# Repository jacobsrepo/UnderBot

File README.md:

# UnderBot

Robot models, ROS 2 / Foxglove station, perception and memory, navigation simulation, and electrical design sources. Existing development lines are preserved; see [the project map](docs/PROJECT_MAP.md) for their roles and [local setup](docs/LOCAL_SETUP.md) for this PC's working installations.

## Components

| Folder | Purpose |
| --- | --- |
| `compact_lab_rover/` | Original parametric rover URDF, RViz configuration and model generator |
| `robot_station/` | ROS gateway, telemetry demo, Qwen chat, bounded world state, memory integration and navigation executor |
| `robot-station-extension/` | Foxglove controls, chat, simulation navigation and telemetry UI |
| `perception/` | EMEET camera/YOLO pipeline, audio transport, Pi communications and PostgreSQL recognition memory |
| `navigation/` | Sample-map preparation, derived demo map, Foxglove layout and navigation documentation |
| `hardware/electrical/` | Versioned KiCad schematics, carrier/PCB designs, budgets and review reports |
| `models/` | Preserved R08/R09 packages, final exports and historical FreeCAD concepts |
| `desktop/` | Cortex desktop assistant, imported with its complete development history |
| `ros2_subsystem/` | Alternative ROS 2 workspace, dashboard and VLA node |
| `website/` | Project website and navigation demonstration video |
| `tools/windows/` | Preserved Windows launchers, deployment overrides and shared ROS environment manifest |

## Getting started

- [Station setup and topic contract](robot_station/README.md)
- [Qwen chat and memory behavior](robot_station/AI_CHAT.md)
- [Navigation simulation and supported commands](navigation/README.md)
- [Camera, audio and perception](perception/README.md)
- [Recognition memory](perception/memory/README.md)
- [Electrical design and revision history](hardware/electrical/README.md)
- [Team workflow](CONTRIBUTING.md)

## Implementation boundaries

Camera and audio pipelines can use real devices. Navigation demonstrations use simulated robot pose and motion on a sample map; they are not physical navigation, SLAM or validated robot dynamics. General chat uses Ollama when configured. Recognition memory requires private database configuration and enrollment. Hardware forwarding remains disabled by default.

The repository contains alternative robot models and implementation lines, not a single fully integrated autonomous robot. Electrical review reports and CAD checks do not establish hardware ratings or readiness to energize. Existing documentation records historical tests; see [current validation](docs/VALIDATION.md) for checks performed during consolidation.

Dependencies, credentials, personal memory databases, recordings and local tool installations are excluded from Git. Original source revisions and development branches remain available. MATLAB/Simulink modelling is the next task and has not been started here.

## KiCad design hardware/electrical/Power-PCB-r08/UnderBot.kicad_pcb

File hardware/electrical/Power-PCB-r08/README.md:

# UnderBot power-distribution PCB r08

**UNROUTED PLACEMENT DRAFT — NOT FOR FABRICATION.** This is the first physical PCB artifact, not a working board. No Gerbers released. All converter modules are external, connected by rated harnesses; this board distributes fused nominal12V. It does not yet mount converters or generate5V/3.3V itself.

## Board and circuit
100 x90 mm outline; two copper layers proposed; four3.2mm mounting holes. Six2-way terminals and four MINI fuse holders. Footprints have assigned nets and schematic references. Ratsnest/unconnected DRC findings are expected because copper routing has deliberately not been finalized before protection/current/connector review. A3 circuit PDF accompanies the PCB.

J1 pin1 = protected input positive; pin2 = ground. NOCO approved accessory cable, external main fuse, disconnect and qualified polarity protection are REQUIRED before J1; this PCB does not implement those yet.

J2 pin1 = positive send to EXTERNAL stop power contact; pin2 = switched positive return. **Neither J2 terminal is ground.** A permanent bridge would defeat the intended stop architecture. The external normally-open contact must have a qualified hardwired manual-reset controller. This circuit does not implement a complete emergency-stop system.

J3 pin1 = fused supply to Pi module, J4 pin1 = fused supply to Kinect conditioner, J5 pin1 = fused supply to Adeept VIN, J6 pin1 = fused supply to auxiliary converter. Pin2 of J3-J6 is ground. Actual auxiliary converter, connector wire sizes and fuse values pending qualification. All auxiliary power (including audio) now stops with arm power, so camera pan/tilt has no live auxiliary bypass. Pi and Kinect remain powered while the external motion contact opens.

T12 remains independent: the board does not stop its wheels. Its separate drive-stop interface must be resolved. Adeept USB VBUS must be blocked without interrupting required data; otherwise Pi USB can bypass arm power interruption.

## Specific component progress
- Six Phoenix1715721 5.08mm screw terminals selected as footprint candidates. Manufacturer nominal current is17.5A under specified conditions; this does NOT rate PCB traces or connected wires.
- Four Keystone3568 MINI fuse holders selected as footprint candidates.
- Littelfuse29732V MINI fuse family selected; exact amperages intentionally not guessed. The linked5A part demonstrates the family, NOT a released fuse choice for all branches.
- Pololu D24V50F5 is a concrete auxiliary5V candidate, specified typical up to5A with thermal limits. Its current USD32.95 listing exceeds the old EUR15 allowance; the shopping budget needs a landed quote before substitution. Do not claim current r07 total includes this price.
- Kinect converter and stop/reset hardware remain open selections.

## Before routing/release
Check mounting envelope and cable exit directions; compare terminal/fuse mechanical drawings; verify input polarity protection; measure NOCO output envelope and interruption behaviour; verify arm revision/backfeed/peaks, Kinect label/startup and pan/tilt load; choose stop power contacts and wire/fuse coordination; then set copper thickness/width/clearance and route. No trace ampacity or total PCB current rating is claimed at placement stage.

Next PCB step is routing once those design inputs are defensible. There are no purchases, fabrication uploads or live hardware changes in this revision.

## Verification result
Schematic exported to PDF; PCB loads and renders;14 footprints with assigned nets and zero routed tracks confirmed. CLI DRC did not finish promptly in either sandboxed or elevated run; both were cancelled. No DRC pass or manufacture readiness is claimed.

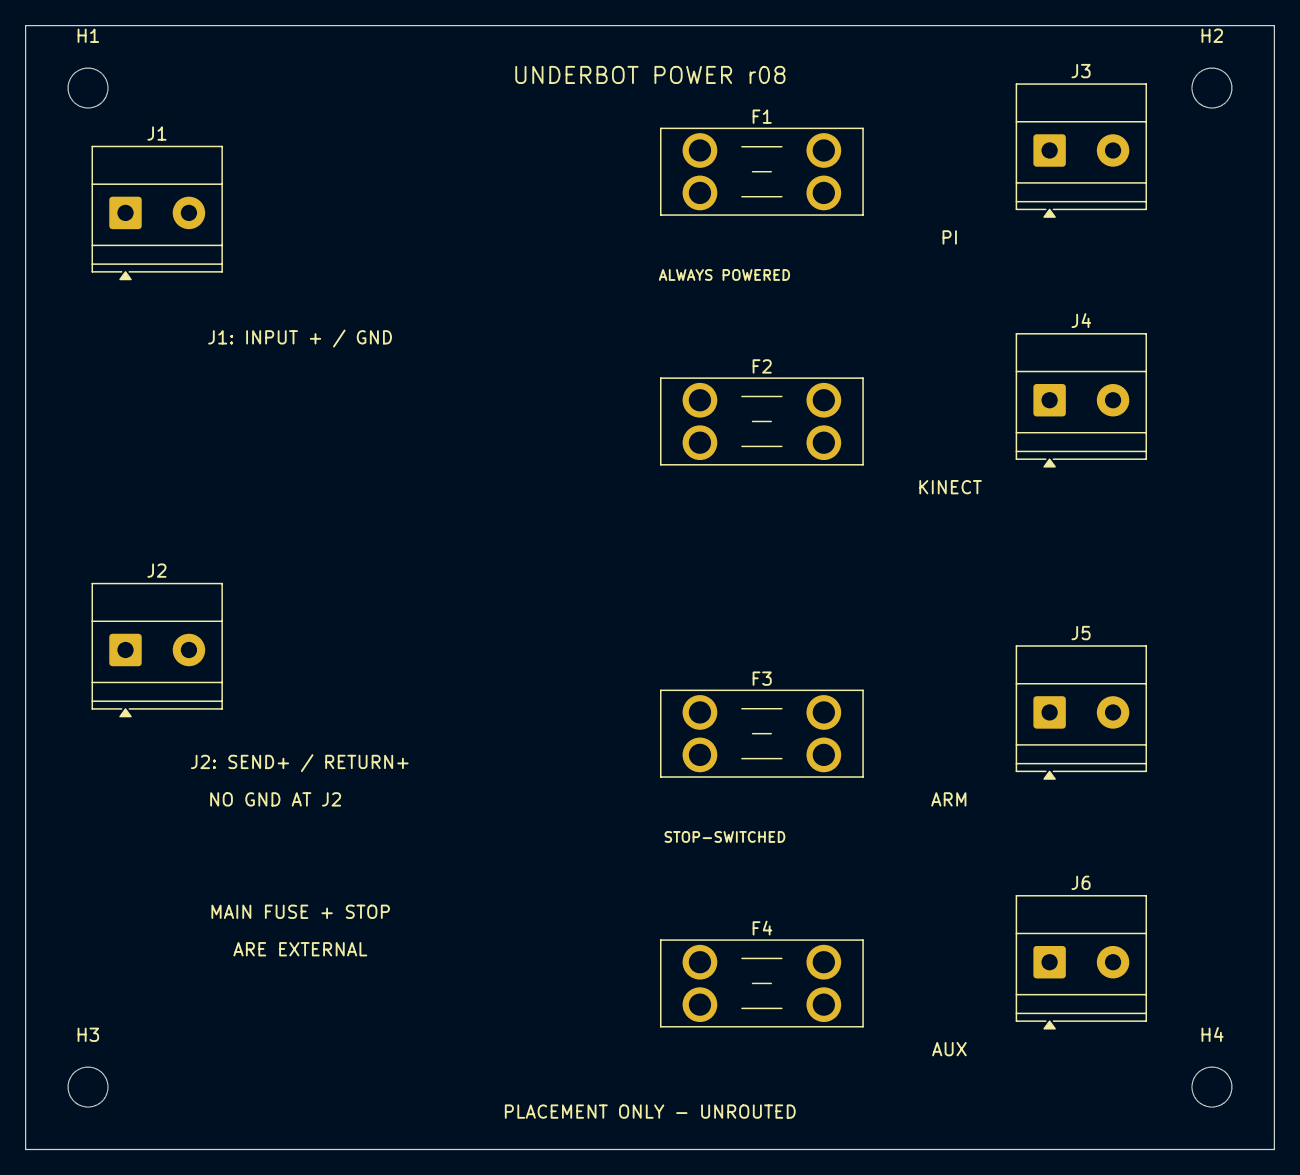
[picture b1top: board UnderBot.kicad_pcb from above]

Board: 2 copper layers, 100.0 x 90.0 mm, 14 parts (0 on the bottom side), 7 nets, no tracks yet.

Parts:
F1, F2, F3, F4: Keystone3568 / fuse TBD; Fuseholder_Blade_Mini_Keystone_3568
H1, H2, H3, H4: M3; MountingHole_3.2mm_M3
J1: Phoenix 1715721 INPUT; TerminalBlock_Phoenix_MKDS-1,5-2-5.08_1x02_P5.08mm_Horizont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
J2: Phoenix 1715721 STOP LOOP; TerminalBlock_Phoenix_MKDS-1,5-2-5.08_1x02_P5.08mm_Horizont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
J3: Phoenix1715721 PI MODULE; TerminalBlock_Phoenix_MKDS-1,5-2-5.08_1x02_P5.08mm_Horizont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
J4: Phoenix1715721 KINECT CONDITIONER; TerminalBlock_Phoenix_MKDS-1,5-2-5.08_1x02_P5.08mm_Horizont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
J5: Phoenix1715721 ARM VIN; TerminalBlock_Phoenix_MKDS-1,5-2-5.08_1x02_P5.08mm_Horizont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
J6: Phoenix1715721 AUX CONVERTER; TerminalBlock_Phoenix_MKDS-1,5-2-5.08_1x02_P5.08mm_Horizont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

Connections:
ACT_SWITCHED: F3.1, F4.1, J2.2
ARM_12: F3.2, J5.1
AUX_12: F4.2, J6.1
DEPTH_12: F2.2, J4.1
GND_SYS: J1.2, J3.2, J4.2, J5.2, J6.2
PI_12: F1.2, J3.1
VIN_PROTECTED: F1.1, F2.1, J1.1, J2.1
